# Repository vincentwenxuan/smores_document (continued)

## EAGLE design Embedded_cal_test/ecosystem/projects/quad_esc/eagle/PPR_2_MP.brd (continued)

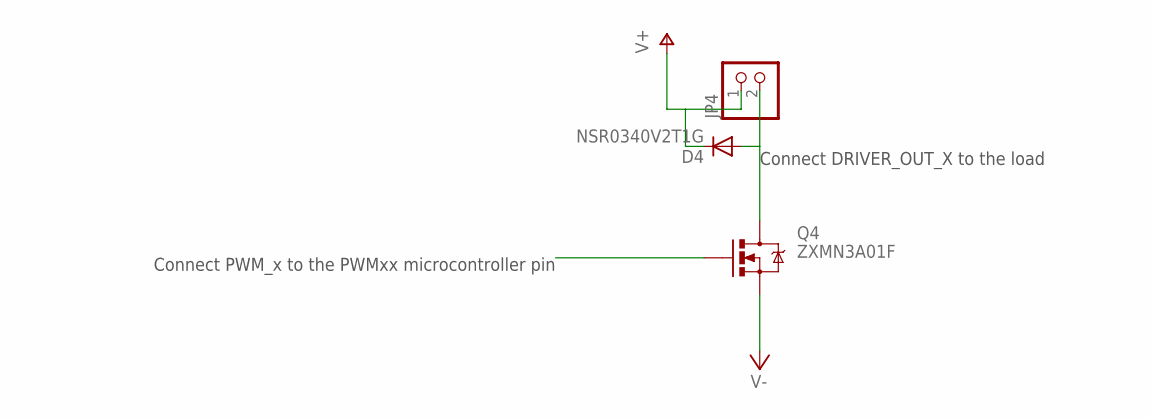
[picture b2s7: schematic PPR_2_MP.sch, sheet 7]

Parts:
D4: NSR0340V2T1G; SOD523
JP4: PINHD-1X2; 1X02
Q4: ZXMN3A01F; SOT23-3

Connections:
DRIVER_OUT_4: D4.A, JP4.2, Q4.3 (D)
PWM_4: Q4.1 (G); also elsewhere on the board
V+: D4.C, JP4.1; also elsewhere on the board
V-: Q4.2 (S); also elsewhere on the board

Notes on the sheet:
Connect PWM_x to the PWMxx microcontroller pin
Connect DRIVER_OUT_X to the load

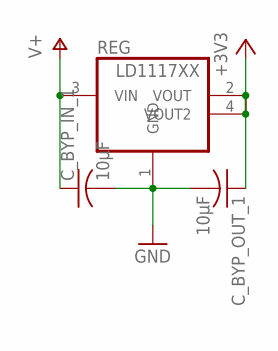
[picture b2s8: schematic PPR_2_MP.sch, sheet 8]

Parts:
C_BYP_IN_1: 10µF; C1206
C_BYP_OUT_1: 10µF; C0603
REG: LD1117XX; SOT-223

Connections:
+3V3: C_BYP_OUT_1.1, REG.2 (VOUT), REG.4 (VOUT2); also elsewhere on the board
GND: C_BYP_IN_1.2, C_BYP_OUT_1.2, REG.1 (GND); also elsewhere on the board
V+: C_BYP_IN_1.1, REG.3 (VIN); also elsewhere on the board

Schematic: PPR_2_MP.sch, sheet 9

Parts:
C_IMU_B_1: .1uF; C0603
C_IMU_CP_1: 2.2nF; C0603
C_IMU_FILT_1: .1uF; C0603
I2C_PULLUP_1, I2C_PULLUP_2: 10k; R0402
U5: TESTING_MPU-6050-1; TESTING_QFN-24-4MM2
VLOGIC_BYPASS_1: 10nF; C0603

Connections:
+3V3: C_IMU_B_1.2, I2C_PULLUP_1.2, I2C_PULLUP_2.2, U5.8 (VLOGIC), U5.13 (VDD), VLOGIC_BYPASS_1.2; also elsewhere on the board
CPOUT_1: C_IMU_CP_1.2, U5.20 (CPOUT)
GND: C_IMU_B_1.1, C_IMU_CP_1.1, C_IMU_FILT_1.1, U5.1 (CLKIN), U5.9 (AD0), U5.11 (FSYNC), U5.18 (GND), VLOGIC_BYPASS_1.1; also elsewhere on the board
IMU_IRQ_1: U5.12 (INT)
IMU_SCL_1: I2C_PULLUP_1.1, U5.23 (SCL); also elsewhere on the board
IMU_SDA_1: I2C_PULLUP_2.1, U5.24 (SDA); also elsewhere on the board
REGOUT_1: C_IMU_FILT_1.2, U5.10 (REGOUT)

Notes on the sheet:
I2C ADDR Select

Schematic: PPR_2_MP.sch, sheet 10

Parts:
JP10: PINHD-1X2; 1X02

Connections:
GND: JP10.2; also elsewhere on the board
V+: JP10.1; also elsewhere on the board

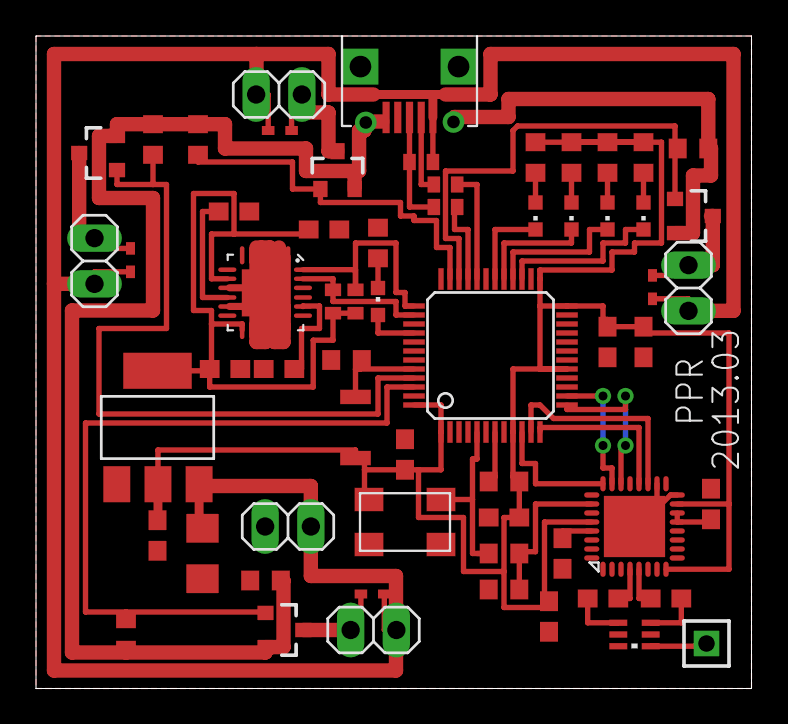
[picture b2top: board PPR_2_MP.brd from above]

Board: 2 copper layers, 39.8 x 36.2 mm, 61 parts (0 on the bottom side), 46 nets.

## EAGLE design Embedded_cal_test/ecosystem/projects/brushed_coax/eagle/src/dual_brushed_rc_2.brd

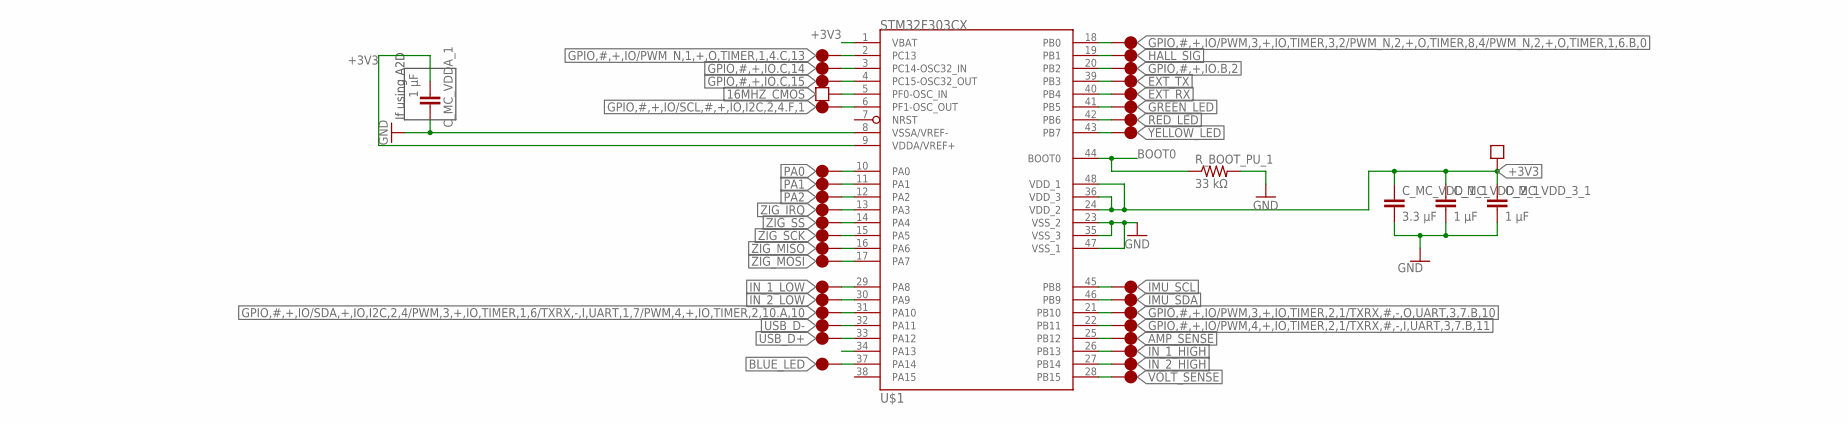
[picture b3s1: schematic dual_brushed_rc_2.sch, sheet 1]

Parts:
C_MC_VDDA_1: 1 µF; C0402
C_MC_VDD_1_1: 3.3 µF; C0603
C_MC_VDD_2_1, C_MC_VDD_3_1: 1 µF; C0402
R_BOOT_PU_1: 33 kΩ; R0402
U$1: STM32F303CX; LQFP48

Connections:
16MHZ_CMOS: U$1.5 (PF0-OSC_IN); also elsewhere on the board
+3V3: C_MC_VDDA_1.1, C_MC_VDD_1_1.1, C_MC_VDD_2_1.1, C_MC_VDD_3_1.1, U$1.1 (VBAT), U$1.9 (VDDA/VREF+), U$1.24 (VDD_2), U$1.36 (VDD_3), U$1.48 (VDD_1); also elsewhere on the board
AMP_SENSE: U$1.25 (PB12); also elsewhere on the board
BLUE_LED: U$1.37 (PA14); also elsewhere on the board
BOOT0: R_BOOT_PU_1.1, U$1.44 (BOOT0); also elsewhere on the board
EXT_RX: U$1.40 (PB4); also elsewhere on the board
EXT_TX: U$1.39 (PB3); also elsewhere on the board
GND: C_MC_VDDA_1.2, C_MC_VDD_1_1.2, C_MC_VDD_2_1.2, C_MC_VDD_3_1.2, R_BOOT_PU_1.2, U$1.8 (VSSA/VREF-), U$1.23 (VSS_2), U$1.35 (VSS_3), U$1.47 (VSS_1); also elsewhere on the board
GPIO,#,+,IO.B,2: U$1.20 (PB2)
GPIO,#,+,IO.C,14: U$1.3 (PC14-OSC32_IN)
GPIO,#,+,IO.C,15: U$1.4 (PC15-OSC32_OUT)
GPIO,#,+,IO/PWM,3,+,IO,TIMER,2,1/TXRX,#,-,O,UART,3,7.B,10: U$1.21 (PB10)
GPIO,#,+,IO/PWM,3,+,IO,TIMER,3,2/PWM_N,2,+,O,TIMER,8,4/PWM_N,2,+,O,TIMER,1,6.B,0: U$1.18 (PB0)
GPIO,#,+,IO/PWM,4,+,IO,TIMER,2,1/TXRX,#,-,I,UART,3,7.B,11: U$1.22 (PB11)
GPIO,#,+,IO/PWM_N,1,+,O,TIMER,1,4.C,13: U$1.2 (PC13)
GPIO,#,+,IO/SCL,#,+,IO,I2C,2,4.F,1: U$1.6 (PF1-OSC_OUT)
GPIO,#,+,IO/SDA,+,IO,I2C,2,4/PWM,3,+,IO,TIMER,1,6/TXRX,-,I,UART,1,7/PWM,4,+,IO,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: U$1.31 (PA10)
GREEN_LED: U$1.41 (PB5); also elsewhere on the board
HALL_SIG: U$1.19 (PB1); also elsewhere on the board
IMU_SCL: U$1.45 (PB8); also elsewhere on the board
IMU_SDA: U$1.46 (PB9); also elsewhere on the board
IN_1_HIGH: U$1.26 (PB13); also elsewhere on the board
IN_1_LOW: U$1.29 (PA8); also elsewhere on the board
IN_2_HIGH: U$1.27 (PB14); also elsewhere on the board
IN_2_LOW: U$1.30 (PA9); also elsewhere on the board
PA0: U$1.10 (PA0)
PA1: U$1.11 (PA1); also elsewhere on the board
PA2: U$1.12 (PA2); also elsewhere on the board
RED_LED: U$1.42 (PB6); also elsewhere on the board
USB_D+: U$1.33 (PA12); also elsewhere on the board
USB_D-: U$1.32 (PA11); also elsewhere on the board
VOLT_SENSE: U$1.28 (PB15); also elsewhere on the board
YELLOW_LED: U$1.43 (PB7); also elsewhere on the board
ZIG_IRQ: U$1.13 (PA3); also elsewhere on the board
ZIG_MISO: U$1.16 (PA6); also elsewhere on the board
ZIG_MOSI: U$1.17 (PA7); also elsewhere on the board
ZIG_SCK: U$1.15 (PA5); also elsewhere on the board
ZIG_SS: U$1.14 (PA4); also elsewhere on the board

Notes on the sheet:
If using A2D

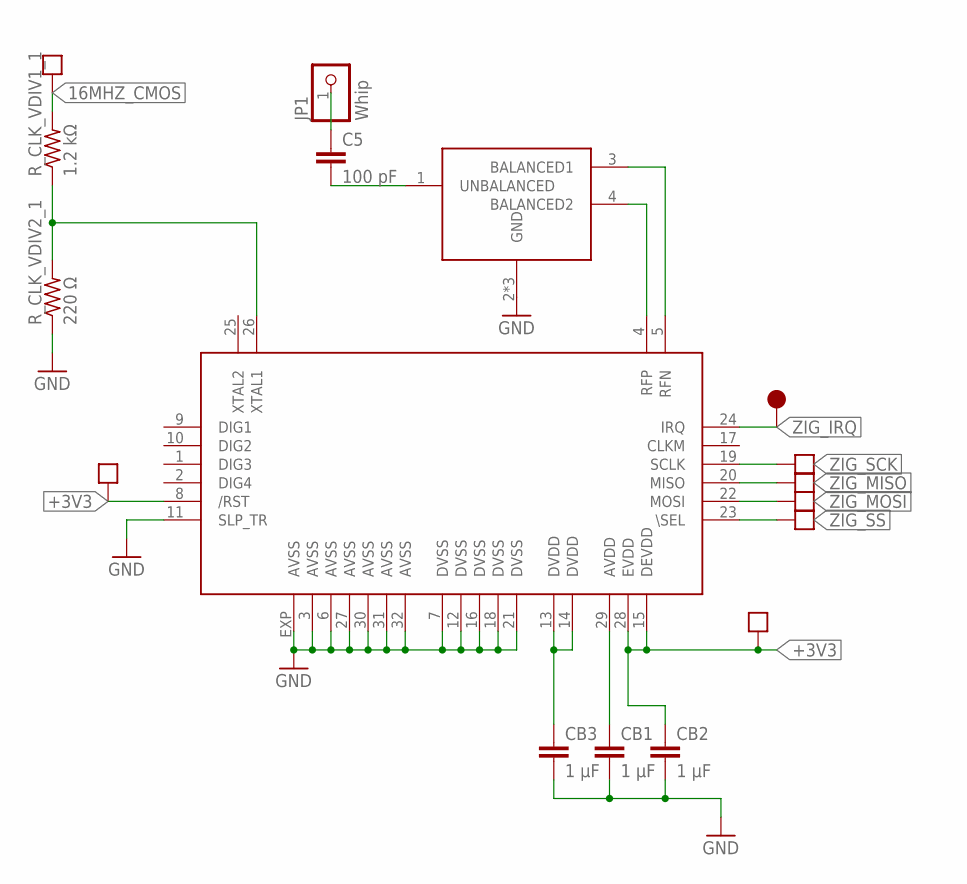
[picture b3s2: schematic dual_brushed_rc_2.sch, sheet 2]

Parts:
BALUN1: 0896FB15A0100
C5: 100 pF; C0402
CB1, CB2, CB3: 1 µF; C0402
JP1: Whip; 1X01
R_CLK_VDIV1_1: 1.2 kΩ; R0402
R_CLK_VDIV2_1: 220 Ω; R0402
U$51: AT86RF; QFNN32

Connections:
16MHZ_0V5_1: R_CLK_VDIV1_1.1, R_CLK_VDIV2_1.2, U$51.26 (XTAL1)
16MHZ_CMOS: R_CLK_VDIV1_1.2; also elsewhere on the board
+3V3: CB2.1, U$51.8 (/RST), U$51.15 (DEVDD), U$51.28 (EVDD); also elsewhere on the board
GND: BALUN1.2 (GND), BALUN1.5 (GND), BALUN1.6 (GND), CB1.2, CB2.2, CB3.2, R_CLK_VDIV2_1.1, U$51.3 (AVSS), U$51.6 (AVSS), U$51.7 (DVSS), U$51.11 (SLP_TR), U$51.12 (DVSS), U$51.16 (DVSS), U$51.18 (DVSS), U$51.21 (DVSS), U$51.27 (AVSS), U$51.30 (AVSS), U$51.31 (AVSS), U$51.32 (AVSS), U$51.EXP (AVSS); also elsewhere on the board
unnamed: BALUN1.1 (UNBALANCED), C5.2
unnamed: C5.1, JP1.1
unnamed: CB3.1, U$51.13 (DVDD), U$51.14 (DVDD)
unnamed: CB1.1, U$51.29 (AVDD)
unnamed: BALUN1.4 (BALANCED2), U$51.4 (RFP)
unnamed: BALUN1.3 (BALANCED1), U$51.5 (RFN)
ZIG_IRQ: U$51.24 (IRQ); also elsewhere on the board
ZIG_MISO: U$51.20 (MISO); also elsewhere on the board
ZIG_MOSI: U$51.22 (MOSI); also elsewhere on the board
ZIG_SCK: U$51.19 (SCLK); also elsewhere on the board
ZIG_SS: U$51.23 (\SEL); also elsewhere on the board

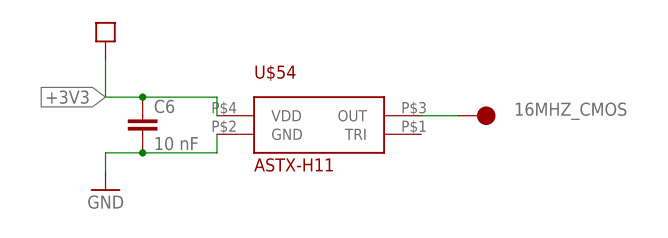
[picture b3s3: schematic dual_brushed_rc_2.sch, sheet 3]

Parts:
C6: 10 nF; C0402
U$54: ASTX-H11

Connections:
16MHZ_CMOS: U$54.P$3 (OUT); also elsewhere on the board
+3V3: C6.1, U$54.P$4 (VDD); also elsewhere on the board
GND: C6.2, U$54.P$2 (GND); also elsewhere on the board

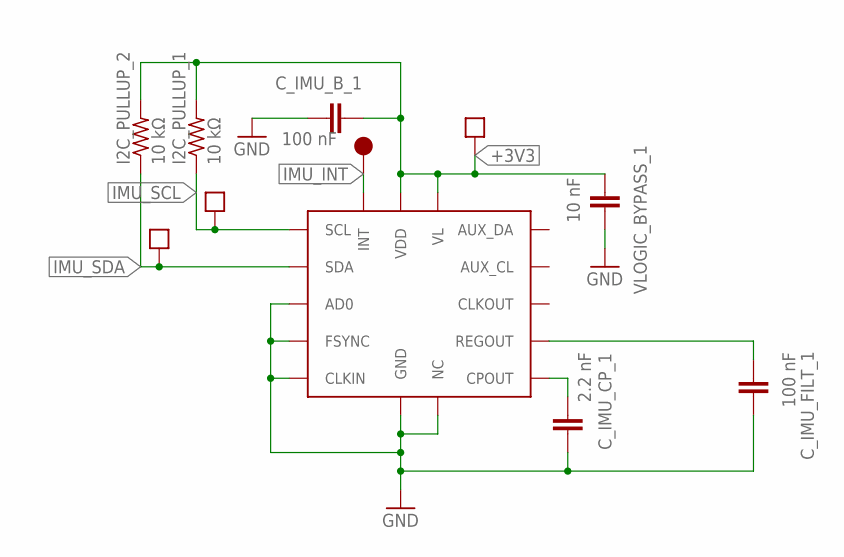
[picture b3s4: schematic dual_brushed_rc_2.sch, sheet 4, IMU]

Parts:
C_IMU_B_1: 100 nF; C0402
C_IMU_CP_1: 2.2 nF; C0402
C_IMU_FILT_1: 100 nF; C0402
I2C_PULLUP_1, I2C_PULLUP_2: 10 kΩ; R0402
U$46: MPU-6050; QFN24
VLOGIC_BYPASS_1: 10 nF; C0402

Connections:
+3V3: C_IMU_B_1.1, I2C_PULLUP_1.2, I2C_PULLUP_2.2, U$46.P$8 (VL), U$46.P$13 (VDD), VLOGIC_BYPASS_1.1; also elsewhere on the board
GND: C_IMU_B_1.2, C_IMU_CP_1.2, C_IMU_FILT_1.2, U$46.P$1 (CLKIN), U$46.P$2 (NC), U$46.P$3 (NC), U$46.P$4 (NC), U$46.P$5 (NC), U$46.P$9 (AD0), U$46.P$11 (FSYNC), U$46.P$14 (NC), U$46.P$15 (NC), U$46.P$16 (NC), U$46.P$17 (NC), U$46.P$18 (GND), U$46.P$25 (GND), VLOGIC_BYPASS_1.2; also elsewhere on the board
IMU_INT: U$46.P$12 (INT)
IMU_SCL: I2C_PULLUP_1.1, U$46.P$23 (SCL); also elsewhere on the board
IMU_SDA: I2C_PULLUP_2.1, U$46.P$24 (SDA); also elsewhere on the board
unnamed: C_IMU_CP_1.1, U$46.P$20 (CPOUT)
REGOUT_1: C_IMU_FILT_1.1, U$46.P$10 (REGOUT)

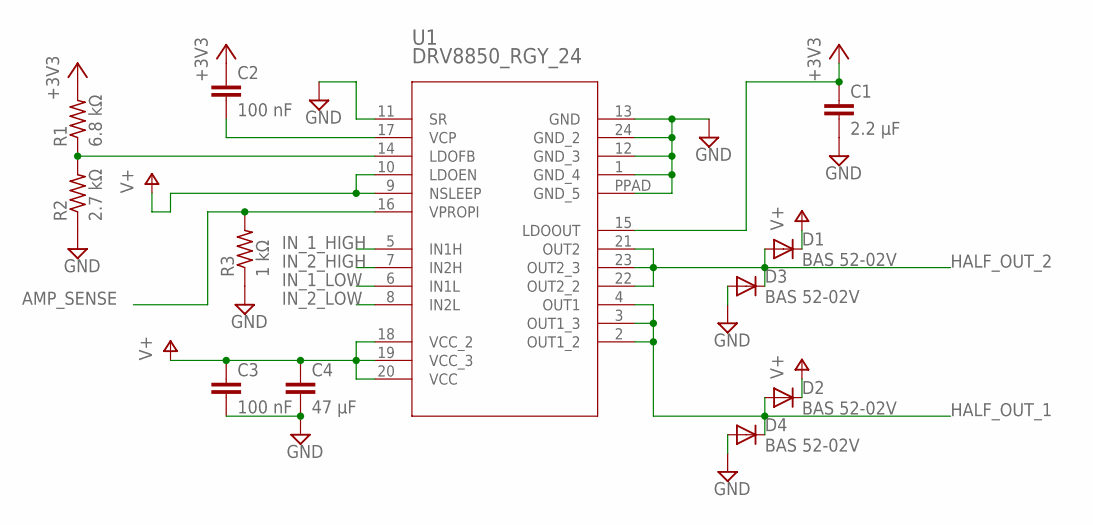
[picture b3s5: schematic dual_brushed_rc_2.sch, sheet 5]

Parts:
C1: 2.2 µF; C0603
C2, C3: 100 nF; C0402
C4: 47 µF; C0805
D1, D2, D3, D4: BAS 52-02V; SOD523
R1: 6.8 kΩ; R0402
R2: 2.7 kΩ; R0402
R3: 1 kΩ; R0402
U1: DRV8850_RGY_24; RGY_24

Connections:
+3V3: C1.1, C2.1, R1.2, U1.15 (LDOOUT); also elsewhere on the board
AMP_SENSE: R3.2, U1.16 (VPROPI); also elsewhere on the board
GND: C1.2, C3.2, C4.2, D3.A, D4.A, R2.1, R3.1, U1.1 (GND_4), U1.11 (SR), U1.12 (GND_3), U1.13 (GND), U1.24 (GND_2), U1.PPAD (GND_5); also elsewhere on the board
HALF_OUT_1: D2.A, D4.C, U1.2 (OUT1_2), U1.3 (OUT1_3), U1.4 (OUT1); also elsewhere on the board
HALF_OUT_2: D1.A, D3.C, U1.21 (OUT2), U1.22 (OUT2_2), U1.23 (OUT2_3); also elsewhere on the board
IN_1_HIGH: U1.5 (IN1H); also elsewhere on the board
IN_1_LOW: U1.6 (IN1L); also elsewhere on the board
IN_2_HIGH: U1.7 (IN2H); also elsewhere on the board
IN_2_LOW: U1.8 (IN2L); also elsewhere on the board
unnamed: R1.1, R2.2, U1.14 (LDOFB)
unnamed: C2.2, U1.17 (VCP)
V+: C3.1, C4.1, D1.C, D2.C, U1.9 (NSLEEP), U1.10 (LDOEN), U1.18 (VCC_2), U1.19 (VCC_3), U1.20 (VCC); also elsewhere on the board

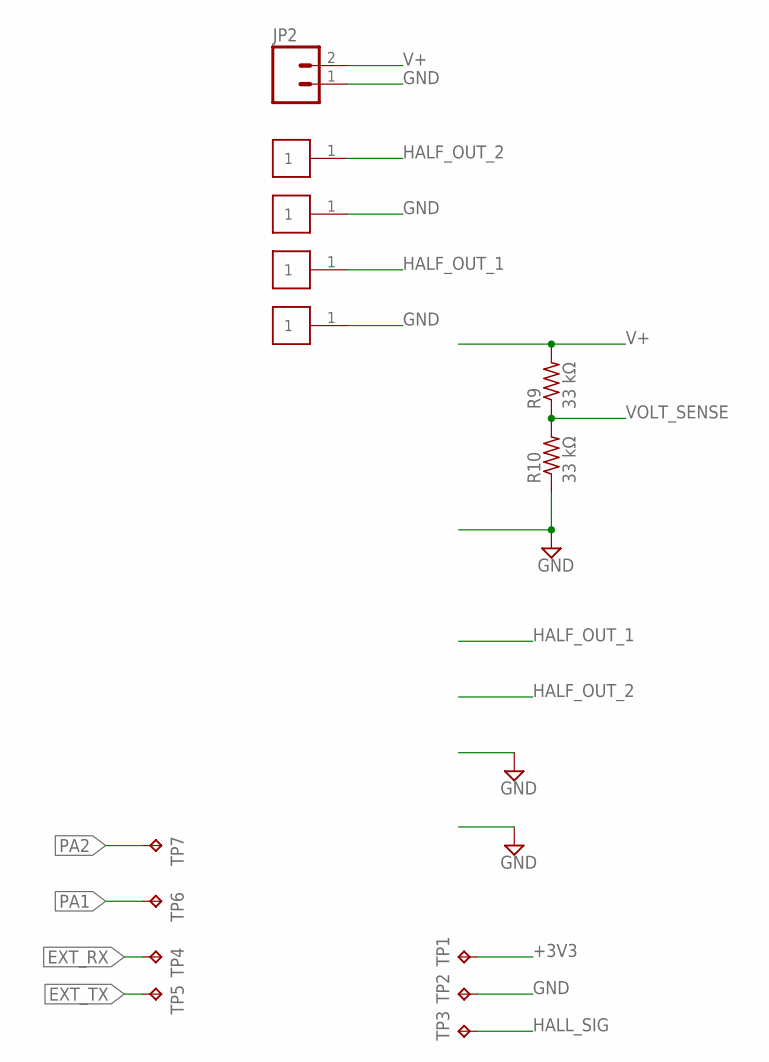
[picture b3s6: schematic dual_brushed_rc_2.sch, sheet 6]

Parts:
JP2: M02-JST-2-PTH-NO_SILK; JST-2-PTH-NS
R9, R10: 33 kΩ; R0402
TP1, TP2, TP3, TP4, TP5, TP6, TP7: TPTP10SQ; TP10SQ
U$55, U$58, U$59, U$60: PADSURF; PAD_1_SURF

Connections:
+3V3: TP1.TP; also elsewhere on the board
EXT_RX: TP4.TP; also elsewhere on the board
EXT_TX: TP5.TP; also elsewhere on the board
GND: JP2.1, R10.1, TP2.TP, U$59.1, U$60.1; also elsewhere on the board
HALF_OUT_1: U$58.1; also elsewhere on the board
HALF_OUT_2: U$55.1; also elsewhere on the board
HALL_SIG: TP3.TP; also elsewhere on the board
PA1: TP6.TP; also elsewhere on the board
PA2: TP7.TP; also elsewhere on the board
V+: JP2.2, R9.2; also elsewhere on the board
VOLT_SENSE: R9.1, R10.2; also elsewhere on the board

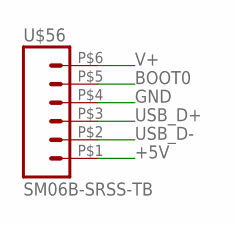
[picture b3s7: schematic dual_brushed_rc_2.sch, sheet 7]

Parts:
U$56: SM06B-SRSS-TB

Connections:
+5V: U$56.P$1 (1)
BOOT0: U$56.P$5 (5); also elsewhere on the board
GND: U$56.P$4 (4); also elsewhere on the board
USB_D+: U$56.P$3 (3); also elsewhere on the board
USB_D-: U$56.P$2 (2); also elsewhere on the board
V+: U$56.P$6 (6); also elsewhere on the board

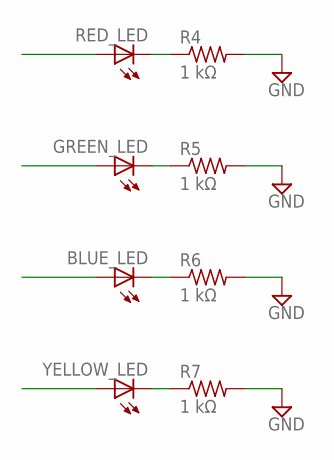
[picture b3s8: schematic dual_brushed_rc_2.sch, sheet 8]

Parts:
BLUE_LED: LEDCHIPLED_0603; CHIPLED_0603
GREEN_LED: LEDCHIPLED_0603; CHIPLED_0603
R4, R5, R6, R7: 1 kΩ; R0402
RED_LED: LEDCHIPLED_0603; CHIPLED_0603
YELLOW_LED: LEDCHIPLED_0603; CHIPLED_0603

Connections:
BLUE_LED: BLUE_LED.A; also elsewhere on the board
GND: R4.2, R5.2, R6.2, R7.2; also elsewhere on the board
GREEN_LED: GREEN_LED.A; also elsewhere on the board
unnamed: R4.1, RED_LED.C
unnamed: GREEN_LED.C, R5.1
unnamed: BLUE_LED.C, R6.1
unnamed: R7.1, YELLOW_LED.C
RED_LED: RED_LED.A; also elsewhere on the board
YELLOW_LED: YELLOW_LED.A; also elsewhere on the board

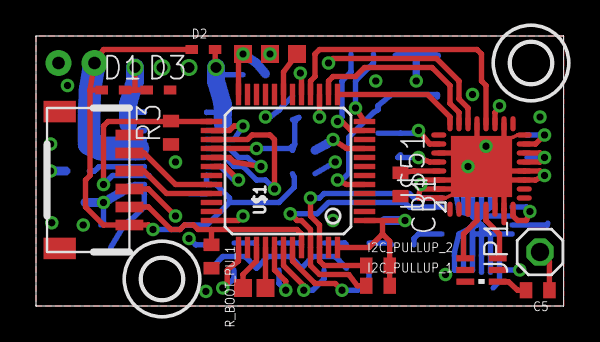
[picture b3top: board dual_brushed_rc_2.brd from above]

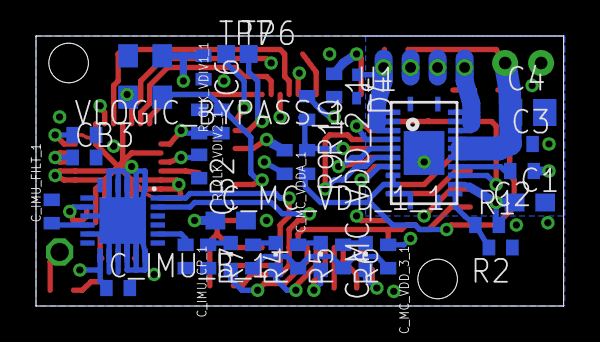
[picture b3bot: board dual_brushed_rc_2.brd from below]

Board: 4 copper layers, 29.3 x 15.0 mm, 61 parts (39 on the bottom side), 46 nets.

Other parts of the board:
U$52, U$57: M2_HOLE_PLASTIC

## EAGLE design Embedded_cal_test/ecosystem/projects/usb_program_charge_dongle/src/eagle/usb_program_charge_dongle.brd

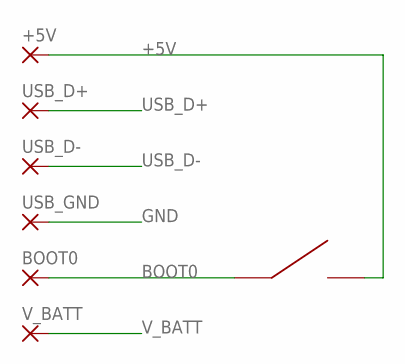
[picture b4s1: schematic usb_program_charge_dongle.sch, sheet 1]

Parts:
+5V: SMD2; SMD1,27-2,54
BOOT0: SMD2; SMD1,27-2,54
SW2: B3U
USB_D+: SMD2; SMD1,27-2,54
USB_D-: SMD2; SMD1,27-2,54
USB_GND: SMD2; SMD1,27-2,54
V_BATT: SMD2; SMD1,27-2,54

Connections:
+5V: +5V.1, SW2.P$2; also elsewhere on the board
BOOT0: BOOT0.1, SW2.P$1
GND: USB_GND.1; also elsewhere on the board
USB_D+: USB_D+.1; also elsewhere on the board
USB_D-: USB_D-.1; also elsewhere on the board
V_BATT: V_BATT.1; also elsewhere on the board

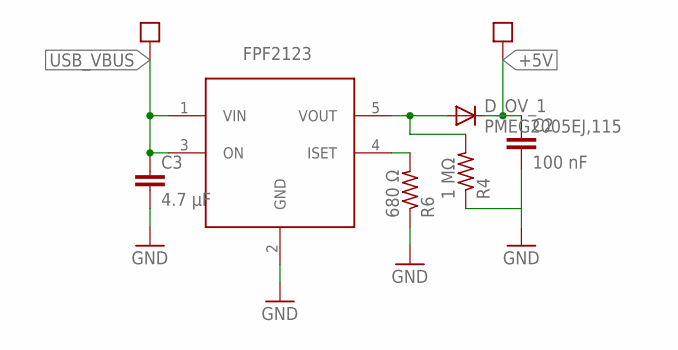
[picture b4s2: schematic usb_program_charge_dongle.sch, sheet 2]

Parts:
C2: 100 nF; C0603
C3: 4.7 µF; C0603
D_OV_1: PMEG2005EJ,115; SOD323-W
FPF2123: FPF2123; SOT23-5L
R4: 1 MΩ; R0603
R6: 680 Ω; R0603

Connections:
+5V: C2.1, D_OV_1.C; also elsewhere on the board
GND: C2.2, C3.2, FPF2123.2 (GND), R4.1, R6.1; also elsewhere on the board
LOAD_ISET_1: FPF2123.4 (ISET), R6.2
unnamed: D_OV_1.A, FPF2123.5 (VOUT), R4.2
USB_VBUS: C3.1, FPF2123.1 (VIN), FPF2123.3 (ON); also elsewhere on the board

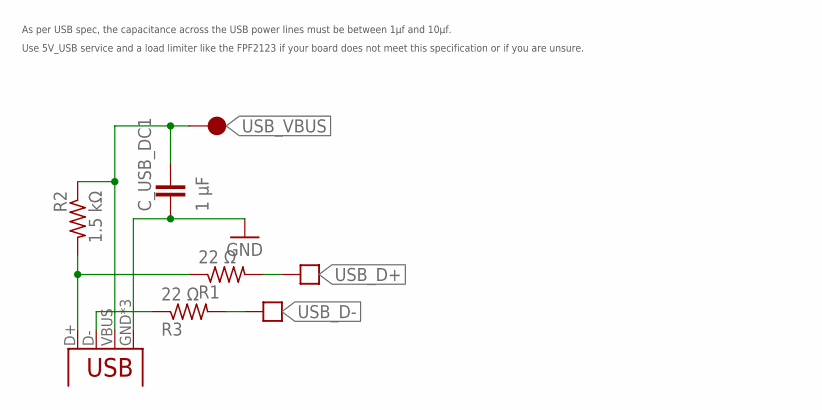
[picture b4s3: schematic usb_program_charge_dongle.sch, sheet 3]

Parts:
C_USB_DC1: 1 µF; C0603
R1, R3: 22 Ω; R0603
R2: 1.5 kΩ; R0603
X1: USB-MICROB

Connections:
D+_IN_1: R1.1, R2.2, X1.D+
D-_IN_1: R3.1, X1.D-
GND: C_USB_DC1.2, X1.GND, X1.MT1 (GND), X1.MT2 (GND); also elsewhere on the board
USB_D+: R1.2; also elsewhere on the board
USB_D-: R3.2; also elsewhere on the board
USB_VBUS: C_USB_DC1.1, R2.1, X1.VBUS; also elsewhere on the board

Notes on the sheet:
As per USB spec, the capacitance across the USB power lines must be between 1µf and 10µf.
Use 5V_USB service and a load limiter like the FPF2123 if your board does not meet this specification or if you are unsure.

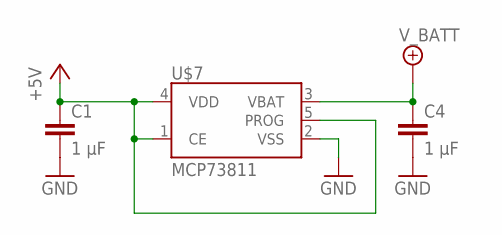
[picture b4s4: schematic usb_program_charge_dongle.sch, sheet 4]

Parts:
C1, C4: 1 µF; C0603
U$7: MCP73811; SOT23-5

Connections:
+5V: C1.1, U$7.1 (CE), U$7.4 (VDD), U$7.5 (PROG); also elsewhere on the board
GND: C1.2, C4.2, U$7.2 (VSS); also elsewhere on the board
V_BATT: C4.1, U$7.3 (VBAT); also elsewhere on the board

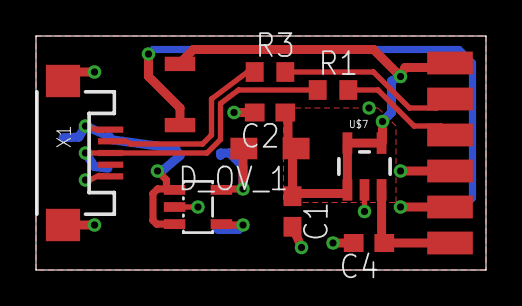
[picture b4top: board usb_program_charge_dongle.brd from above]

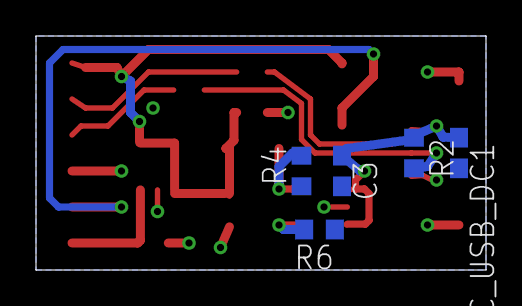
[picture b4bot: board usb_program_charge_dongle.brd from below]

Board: 2 copper layers, 25.0 x 13.0 mm, 21 parts (5 on the bottom side), 11 nets.

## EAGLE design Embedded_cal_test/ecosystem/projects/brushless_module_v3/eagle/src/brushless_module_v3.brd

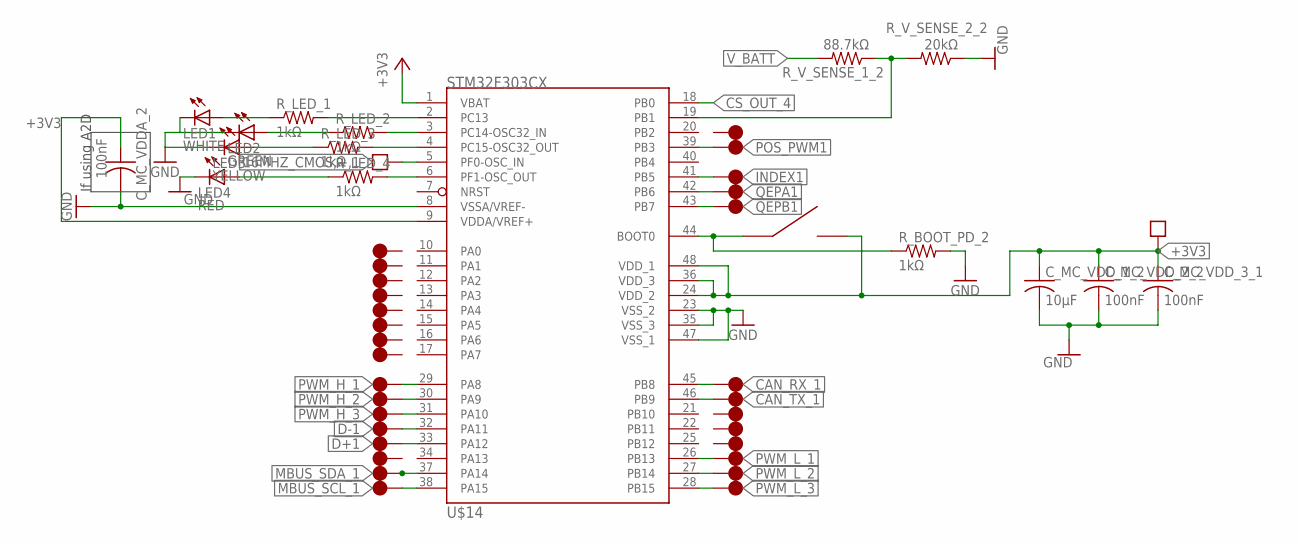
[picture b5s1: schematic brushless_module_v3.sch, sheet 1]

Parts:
C_MC_VDDA_2: 100nF; C0402
C_MC_VDD_1_2: 10µF; C0402
C_MC_VDD_2_2, C_MC_VDD_3_1: 100nF; C0402
LED1: WHITE; 0402
LED2: GREEN; 0402
LED3: YELLOW; 0402
LED4: RED; 0402
R_BOOT_PD_2: 1kΩ; R0402
R_LED_1, R_LED_2, R_LED_3, R_LED_4: 1kΩ; R0402
R_V_SENSE_1_2: 88.7kΩ; R0402
R_V_SENSE_2_2: 20kΩ; R0402
SW2: B3U
U$14: STM32F303CX; LQFP48

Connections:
16MHZ_CMOS,+,1: U$14.5 (PF0-OSC_IN); also elsewhere on the board
+3V3: C_MC_VDDA_2.1, C_MC_VDD_1_2.1, C_MC_VDD_2_2.1, C_MC_VDD_3_1.1, SW2.P$2, U$14.1 (VBAT), U$14.9 (VDDA/VREF+), U$14.24 (VDD_2), U$14.36 (VDD_3), U$14.48 (VDD_1); also elsewhere on the board
BOOT0_2: R_BOOT_PD_2.1, SW2.P$1, U$14.44 (BOOT0)
CAN_RX_1: U$14.45 (PB8); also elsewhere on the board
CAN_TX_1: U$14.46 (PB9); also elsewhere on the board
CS_OUT_4: U$14.18 (PB0); also elsewhere on the board
D+1: U$14.33 (PA12); also elsewhere on the board
D-1: U$14.32 (PA11); also elsewhere on the board
GND: C_MC_VDDA_2.2, C_MC_VDD_1_2.2, C_MC_VDD_2_2.2, C_MC_VDD_3_1.2, LED1.CATHODE (C), LED2.CATHODE (C), LED3.CATHODE (C), LED4.CATHODE (C), R_BOOT_PD_2.2, R_V_SENSE_2_2.1, U$14.8 (VSSA/VREF-), U$14.23 (VSS_2), U$14.35 (VSS_3), U$14.47 (VSS_1); also elsewhere on the board
INDEX1: U$14.41 (PB5); also elsewhere on the board
LED_1: R_LED_1.2, U$14.2 (PC13)
LED_2: R_LED_2.2, U$14.3 (PC14-OSC32_IN)
LED_3: R_LED_3.2, U$14.4 (PC15-OSC32_OUT)
LED_4: R_LED_4.2, U$14.6 (PF1-OSC_OUT)
MBUS_SCL_1: U$14.38 (PA15); also elsewhere on the board
MBUS_SDA_1: U$14.37 (PA14); also elsewhere on the board
unnamed: LED4.ANODE (A), R_LED_4.1
unnamed: LED3.ANODE (A), R_LED_3.1
unnamed: LED2.ANODE (A), R_LED_2.1
unnamed: LED1.ANODE (A), R_LED_1.1
POS_PWM1: U$14.39 (PB3); also elsewhere on the board
PWM_H_1: U$14.29 (PA8); also elsewhere on the board
PWM_H_2: U$14.30 (PA9); also elsewhere on the board
PWM_H_3: U$14.31 (PA10); also elsewhere on the board
PWM_L_1: U$14.26 (PB13); also elsewhere on the board
PWM_L_2: U$14.27 (PB14); also elsewhere on the board
PWM_L_3: U$14.28 (PB15); also elsewhere on the board
QEPA1: U$14.42 (PB6); also elsewhere on the board
QEPB1: U$14.43 (PB7); also elsewhere on the board
VS_OUT: R_V_SENSE_1_2.1, R_V_SENSE_2_2.2, U$14.19 (PB1)
V_BATT: R_V_SENSE_1_2.2; also elsewhere on the board

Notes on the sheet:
If using A2D

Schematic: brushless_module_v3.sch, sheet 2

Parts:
C_DC_ENC1_1: 10µF; C0402
C_DC_ENC2_1: 100nF; C0402
ENC1: AS5040; SSOP16
LED_MAG_G1: GREEN; 0402
LED_MAG_Y1: YELLOW; 0402
LED_POS1: BLUE; 0402
R_MAG_G1: 1kΩ; R0402
R_MAG_Y1: 1kΩ; R0402
R_POS1: 1kΩ; R0402

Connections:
+3V3: C_DC_ENC2_1.1, ENC1.16 (VDD5V), R_MAG_G1.2, R_MAG_Y1.2; also elsewhere on the board
ENC_3V3_1: C_DC_ENC1_1.1, ENC1.15 (VDD3V3)
GND: C_DC_ENC1_1.2, C_DC_ENC2_1.2, ENC1.7 (VSS), ENC1.8 (PROG), ENC1.11 (CSN), LED_MAG_G1.CATHODE (C), LED_MAG_Y1.CATHODE (C), R_POS1.1; also elsewhere on the board
INDEX1: ENC1.6 (INDEX_W); also elsewhere on the board
MAGDEC1: ENC1.2 (MAGDEC), LED_MAG_Y1.ANODE (A), R_MAG_Y1.1
MAGINC1: ENC1.1 (MAGINC), LED_MAG_G1.ANODE (A), R_MAG_G1.1
unnamed: LED_POS1.ANODE (A), R_POS1.2
POS_PWM1: ENC1.12 (PWN), LED_POS1.CATHODE (C); also elsewhere on the board
QEPA1: ENC1.3 (A_LSB_U); also elsewhere on the board
QEPB1: ENC1.4 (B_DIR_V); also elsewhere on the board

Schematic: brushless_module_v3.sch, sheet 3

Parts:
CS_4: INA21X; SC70
C_CS_DC_4: 100nF; C0402
C_S_1: 10µF; C0402
R_CS_4: 1mΩ; R1206
R_CS_REF1_4, R_CS_REF2_4: 10kΩ; R0402
R_S1_1, R_S2_1: 10Ω; R0402

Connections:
+3V3: R_CS_REF1_4.2; also elsewhere on the board
CS_OUT_4: CS_4.P6 (OUT); also elsewhere on the board
GND: CS_4.P2 (GND), C_CS_DC_4.2, R_CS_REF2_4.1; also elsewhere on the board
IN+_1: CS_4.P4 (IN+), C_S_1.1, R_S2_1.1
IN-_1: CS_4.P5 (IN-), C_S_1.2, R_S1_1.1
V+: R_CS_4.1, R_S1_1.2; also elsewhere on the board
V_BATT: CS_4.P3 (V+), C_CS_DC_4.1, R_CS_4.2, R_S2_1.2; also elsewhere on the board
V_REF_CS: CS_4.P1 (REF), R_CS_REF1_4.1, R_CS_REF2_4.2

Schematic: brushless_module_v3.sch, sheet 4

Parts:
C3: 10µF; C0402
D_OV_1: PMEG2005EJ,115; SOD323-W
FPF2123: FPF2123; SOT23-5L
R4: 1MΩ; R0402
R6: 604Ω; R0402

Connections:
+5V: C3.1, FPF2123.1 (VIN), FPF2123.3 (ON); also elsewhere on the board
GND: C3.2, FPF2123.2 (GND), R4.1, R6.1; also elsewhere on the board
LOAD_ISET_1: FPF2123.4 (ISET), R6.2
unnamed: D_OV_1.A, FPF2123.5 (VOUT), R4.2
V_BATT: D_OV_1.C; also elsewhere on the board

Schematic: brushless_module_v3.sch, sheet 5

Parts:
R11, R12: 1kΩ; R0402
U$57: SM06B-SRSS-TB

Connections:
+3V3: R11.2, R12.2, U$57.P$3 (3); also elsewhere on the board
CAN_H_1: U$57.P$6 (6); also elsewhere on the board
CAN_L_1: U$57.P$5 (5); also elsewhere on the board
GND: U$57.P$1 (1); also elsewhere on the board
MBUS_SCL_1: R12.1, U$57.P$2 (2); also elsewhere on the board
MBUS_SDA_1: R11.1, U$57.P$4 (4); also elsewhere on the board

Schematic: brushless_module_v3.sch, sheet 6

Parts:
U$9: DEANS-MICRO-3PIN

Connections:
INV_OUT1: U$9.P$1 (1); also elsewhere on the board
INV_OUT2: U$9.P$3 (3); also elsewhere on the board
INV_OUT3: U$9.P$2 (2); also elsewhere on the board

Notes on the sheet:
Done with vias because no pinhead was proper size

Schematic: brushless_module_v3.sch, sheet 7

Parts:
C6: 100nF; C0402
U$54: ASTX-H11

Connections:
16MHZ_CMOS,+,1: U$54.P$3 (OUT); also elsewhere on the board
+3V3: C6.1, U$54.P$4 (VDD); also elsewhere on the board
GND: C6.2, U$54.P$2 (GND); also elsewhere on the board

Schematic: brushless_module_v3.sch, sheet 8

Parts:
CIN_1: 10µF; C0603
COUT_1: 22µF; C0603
D_UV_2: PMEG2005EJ,115; SOD323-W
L1: 2.2µH; L2012C
MMSZ4684T1G1: D-SOD123; SOD123
U$37: TPS621XX; 8-WFDFN

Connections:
+3V3: COUT_1.1, L1.2, MMSZ4684T1G1.1 (C), U$37.P$6 (VOS); also elsewhere on the board
GND: CIN_1.2, COUT_1.2, D_UV_2.A, MMSZ4684T1G1.2 (A), U$37.P$1 (PGND), U$37.P$4 (AGND), U$37.P$5 (FB), U$37.P$9 (AGND); also elsewhere on the board
GPIO,#,+,O: U$37.P$8 (PG)
unnamed: L1.1, U$37.P$7 (SW)
V+: CIN_1.1, D_UV_2.C, U$37.P$2 (VIN), U$37.P$3 (EN); also elsewhere on the board

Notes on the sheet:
The GPIO is an open drain and requires a pull up or a micro's internal pull up

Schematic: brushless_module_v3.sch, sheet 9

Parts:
R5: 1.5kΩ; R0402
R7, R8: 22Ω; R0402
X1: USB-MICROB

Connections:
+5V: R5.1, X1.VBUS; also elsewhere on the board
D+1: R7.2; also elsewhere on the board
D+_IN_2: R5.2, R7.1, X1.D+
D-1: R8.2; also elsewhere on the board
D-_IN_2: R8.1, X1.D-
GND: X1.GND, X1.MT1 (GND), X1.MT2 (GND); also elsewhere on the board

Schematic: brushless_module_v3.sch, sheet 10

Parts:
CAN_TRAN1: MAX3051; SOT23-8L
C_CAN_DC1: 100nF; C0402
R_RS1: 10kΩ; R0402

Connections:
+3V3: CAN_TRAN1.3 (VCC), C_CAN_DC1.1; also elsewhere on the board
CAN_H_1: CAN_TRAN1.7 (CANH); also elsewhere on the board
CAN_L_1: CAN_TRAN1.6 (CANL); also elsewhere on the board
CAN_RX_1: CAN_TRAN1.4 (RXD); also elsewhere on the board
CAN_TX_1: CAN_TRAN1.1 (TXD); also elsewhere on the board
GND: CAN_TRAN1.2 (GND), CAN_TRAN1.5 (SHDN), C_CAN_DC1.2, R_RS1.1; also elsewhere on the board
unnamed: CAN_TRAN1.8 (RS), R_RS1.2

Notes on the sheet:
Optional
R_RS (kΩ) = 12000 / (maximum speed in kbps)

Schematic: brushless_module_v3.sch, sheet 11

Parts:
C1: 47µF; C1206
D_FLYBACK1_1, D_FLYBACK2_1: BAS 52-02V H6327; SOD523
R_SLEW_H_1: 1Ω; R0402
R_SLEW_L_1: 1Ω; R0402
U$62: SI7139DP-T1-GE3; S0-8-POWERPAK
U$63: SIR466DP-T1-GE3; S0-8-POWERPAK
U$64: UCC2752XUCC27524DSD; 8-WDFN

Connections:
DRIVER_OUT_H_1: R_SLEW_H_1.1, U$64.P5 (OUTB)
DRIVER_OUT_L_1: R_SLEW_L_1.1, U$64.P7 (OUTA)
GATE_H_1: R_SLEW_H_1.2, U$62.4 (G)
GATE_L_1: R_SLEW_L_1.2, U$63.4 (G)
GND: C1.2, D_FLYBACK2_1.A, U$63.1 (S), U$63.2 (S), U$63.3 (S), U$64.EP (GND), U$64.P3 (GND); also elsewhere on the board
INV_OUT1: D_FLYBACK1_1.A, D_FLYBACK2_1.C, U$62.5 (D), U$62.6 (D), U$62.7 (D), U$62.8 (D), U$62.P$1 (D), U$63.5 (D), U$63.6 (D), U$63.7 (D), U$63.8 (D), U$63.P$1 (D); also elsewhere on the board
PWM_H_1: U$64.P2 (INA); also elsewhere on the board
PWM_L_1: U$64.P4 (INB); also elsewhere on the board
V+: C1.1, D_FLYBACK1_1.C, U$62.1 (S), U$62.2 (S), U$62.3 (S), U$64.P6 (VDD); also elsewhere on the board

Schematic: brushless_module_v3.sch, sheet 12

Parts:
C4: 47µF; C1206
D_FLYBACK1_2, D_FLYBACK2_2: BAS 52-02V H6327; SOD523
R_SLEW_H_2: 1Ω; R0402
R_SLEW_L_2: 1Ω; R0402
U$71: SI7139DP-T1-GE3; S0-8-POWERPAK
U$72: SIR466DP-T1-GE3; S0-8-POWERPAK
U$73: UCC2752XUCC27524DSD; 8-WDFN

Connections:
DRIVER_OUT_H_2: R_SLEW_H_2.1, U$73.P7 (OUTA)
DRIVER_OUT_L_2: R_SLEW_L_2.1, U$73.P5 (OUTB)
GATE_H_2: R_SLEW_H_2.2, U$71.4 (G)
GATE_L_2: R_SLEW_L_2.2, U$72.4 (G)
GND: C4.2, D_FLYBACK2_2.A, U$72.1 (S), U$72.2 (S), U$72.3 (S), U$73.EP (GND), U$73.P3 (GND); also elsewhere on the board
INV_OUT2: D_FLYBACK1_2.A, D_FLYBACK2_2.C, U$71.5 (D), U$71.6 (D), U$71.7 (D), U$71.8 (D), U$71.P$1 (D), U$72.5 (D), U$72.6 (D), U$72.7 (D), U$72.8 (D), U$72.P$1 (D); also elsewhere on the board
PWM_H_2: U$73.P2 (INA); also elsewhere on the board
PWM_L_2: U$73.P4 (INB); also elsewhere on the board
V+: C4.1, D_FLYBACK1_2.C, U$71.1 (S), U$71.2 (S), U$71.3 (S), U$73.P6 (VDD); also elsewhere on the board

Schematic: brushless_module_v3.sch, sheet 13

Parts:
C5: 47µF; C1206
D_FLYBACK1_3, D_FLYBACK2_3: BAS 52-02V H6327; SOD523
R_SLEW_H_3: 1Ω; R0402
R_SLEW_L_3: 1Ω; R0402
U$80: SI7139DP-T1-GE3; S0-8-POWERPAK
U$81: SIR466DP-T1-GE3; S0-8-POWERPAK
U$82: UCC2752XUCC27524DSD; 8-WDFN

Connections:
DRIVER_OUT_H_3: R_SLEW_H_3.1, U$82.P5 (OUTB)
DRIVER_OUT_L_3: R_SLEW_L_3.1, U$82.P7 (OUTA)
GATE_H_3: R_SLEW_H_3.2, U$80.4 (G)
GATE_L_3: R_SLEW_L_3.2, U$81.4 (G)
GND: C5.2, D_FLYBACK2_3.A, U$81.1 (S), U$81.2 (S), U$81.3 (S), U$82.EP (GND), U$82.P3 (GND); also elsewhere on the board
INV_OUT3: D_FLYBACK1_3.A, D_FLYBACK2_3.C, U$80.5 (D), U$80.6 (D), U$80.7 (D), U$80.8 (D), U$80.P$1 (D), U$81.5 (D), U$81.6 (D), U$81.7 (D), U$81.8 (D), U$81.P$1 (D); also elsewhere on the board
PWM_H_3: U$82.P2 (INA); also elsewhere on the board
PWM_L_3: U$82.P4 (INB); also elsewhere on the board
V+: C5.1, D_FLYBACK1_3.C, U$80.1 (S), U$80.2 (S), U$80.3 (S), U$82.P6 (VDD); also elsewhere on the board
